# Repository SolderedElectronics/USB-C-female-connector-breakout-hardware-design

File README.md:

# USB-C female connector breakout Hardware Design

## About the Product

|  |
| :----------------------------------------------------------: |
| [Buy USB-C female connector breakout](https://www.solde.red/333011) |

The USB Type-C is ubiquitous. We always wanted to add it to our electronics projects, and we’re sure you did too. Adding a USB Type-C connector to your projects is easier than ever thanks to this USB Type-C breakout board. It will allow you to send data to your device, as well as add power to the circuit.

The USB Type-C connector’s GND, CC2, SBU2, D-, D+, SBU1, CC1, and VUSB pins are broken out to the plated through-holes.

---

## Repository Contents

This repository contains all design files for USB-C female connector breakout, organized as follows:

- **`CAD` folder**: Contains KiCAD design files, including:
  - Schematics
  - PCB layout
  - Panel PCB layout
  - Source 3D files in Fusion360, if any
  - All files are sorted by version with a detailed change log.
- **`OUTPUTS` folder**: Includes all production-ready files, such as:
  - Bill of Materials (BOM) and interactive BOM (iBOM)
  - PDF versions of schematics
  - 3D `.step` file of the board
  - 3D-printable models
  - Gerber files for PCB manufacturing
  - Image of the pinout of the board
  - Product image
  - Compliance, legal and generic sales documents

Refer to the `Change Log` in the CAD folder for details about updates between versions.

---

## Learn More About the Product

Beyond the repository, explore the following resources:

### Soldered Verify

The **Soldered Verify** system ensures every board you purchase from Soldered is fully functional. It also provides access to exclusive test data for your product. To get started, find the unique Soldered Verify ID on your product's packaging and enter the ID on the [Soldered Verify page](https://soldered.com/verify/) to access test results and additional product details.

### Soldered Community

Soldered Community is your go-to place for technical support. Our engineers track and answer all questions posted there, and it’s a great space for the maker community. Get answers to your questions and solutions for your challenges at [Soldered Community](https://soldered.com/community).

### solde.red

solde.red is an ultimate URL shortener and information hub. Access it by typing solde.red/ followed by your product SKU, e.g., [solde.red/333000](https://solde.red/333000), to find getting-started guides, datasheets, open-source hardware and software files, certifications, images, pinouts, and more. Read more about the shortener [here](https://solde.red/info/).

---

## Contributing

Contributions are welcome! Here’s how you can get involved:

- Submit pull requests to enhance the design or fix issues.
- Report bugs or problems by opening an issue.

We encourage community collaboration to make this product even better.

---

## About Soldered

[Soldered for Makers](https://soldered.com) specializes in designing and manufacturing electronic products tailored for enthusiasts, ranging from hobbyists to professionals. Our portfolio includes electronic boards, sensors, and actuators that are widely utilized in fields such as microelectronics, mechatronics, robotics, programming, and IoT. Every product we offer is designed in-house and built upon open-source hardware and software platforms. Proudly certified and manufactured within the European Union, our catalog likely includes the product you need for your project.

We complement these products with comprehensive tutorials and manuals, product descriptions, schematics, programming codes, and project examples. Our round-the-clock [customer and technical support](https://soldered.com/community) is available for all our products, irrespective of the sales channel. Soldered’s success and services reflect our maker community’s unwavering [trust](https://www.trustpilot.com/review/soldered.com), for which we are deeply grateful. Join our community and create using Soldered products.

---

## License

All Soldered open-source hardware (OSH) is under The TAPR Open Hardware License. Read more in the LICENSE file located in this repository.

**Disclaimer:**

No warranty - all designs in this repository are distributed in the hope that they will be useful, but without any warranty. They are provided "AS IS", therefore without warranty of any kind, either expressed or implied. The entire quality and performance of what you do with the contents of this repository are your responsibility. In no event Soldered Electronics will be liable for your damages, or losses, including any general, special, incidental, or consequential damage arising out of the use or inability to use the contents of this repository. 

---

## Have fun!

Thank you for your support from your fellow makers at Soldered Electronics.

Happy Making!

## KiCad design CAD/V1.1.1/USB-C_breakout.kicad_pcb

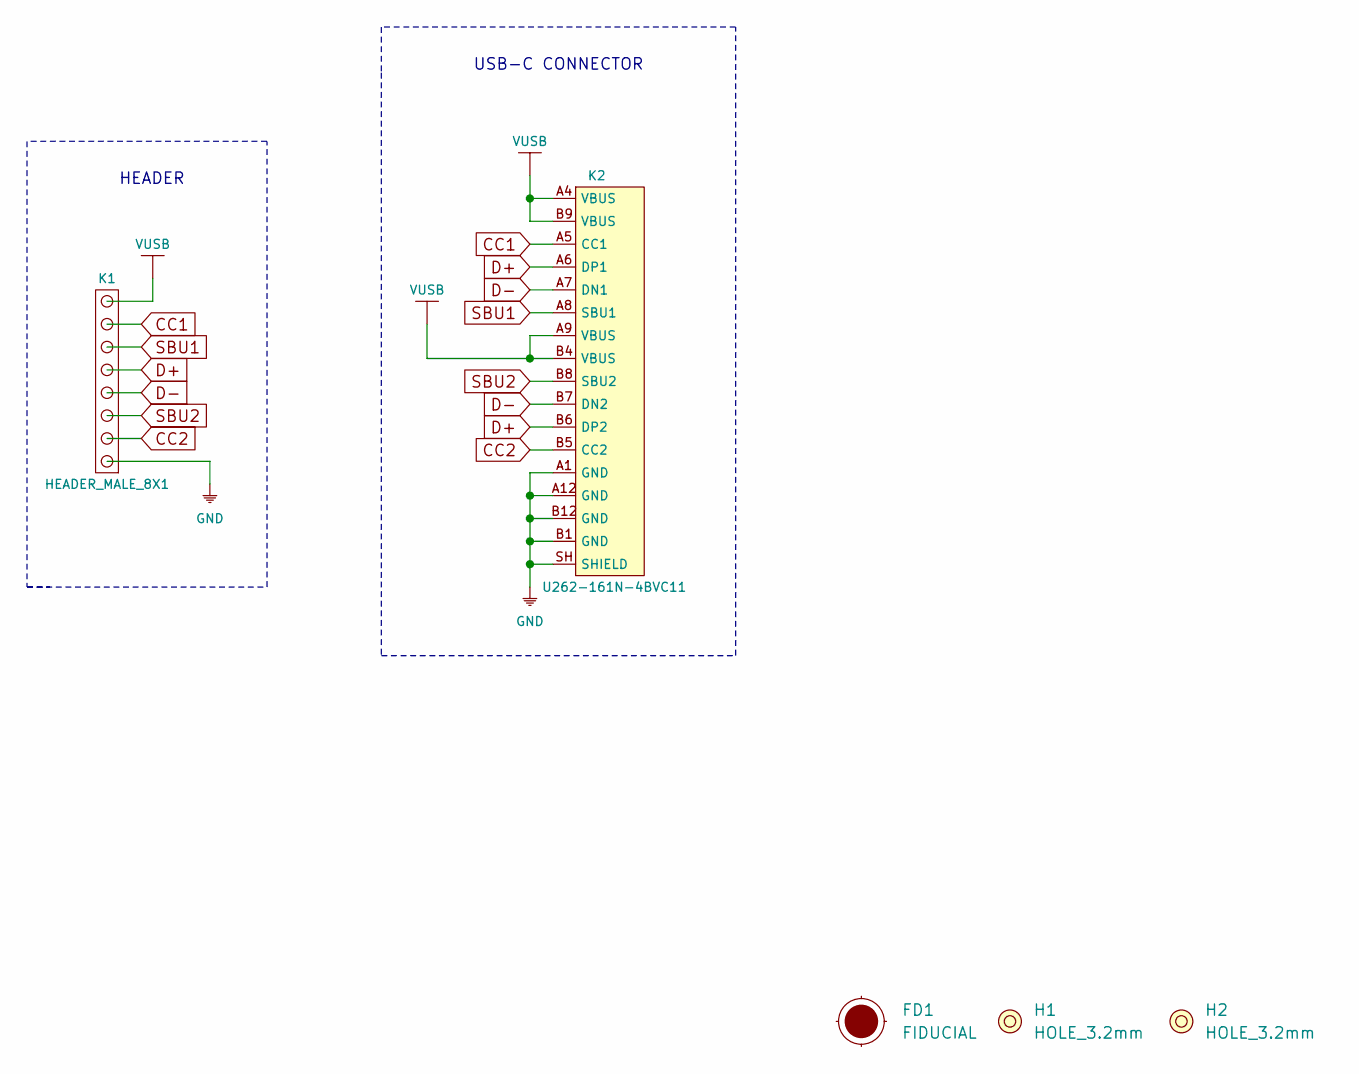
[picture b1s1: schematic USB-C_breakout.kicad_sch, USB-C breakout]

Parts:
FD1: FIDUCIAL; FIDUCIAL_23
H1, H2: HOLE_3.2mm
K1: HEADER_MALE_8X1
K2: U262-161N-4BVC11

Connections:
CC1: K1.7, K2.A5 (CC1)
CC2: K1.2, K2.B5 (CC2)
D+: K1.5, K2.A6 (DP1), K2.B6 (DP2)
D-: K1.4, K2.A7 (DN1), K2.B7 (DN2)
GND: K1.1, K2.A1 (GND), K2.A12 (GND), K2.B1 (GND), K2.B12 (GND), K2.SH (SHIELD)
SBU1: K1.6, K2.A8 (SBU1)
SBU2: K1.3, K2.B8 (SBU2)
VUSB: K1.8, K2.A4 (VBUS), K2.A9 (VBUS), K2.B4 (VBUS), K2.B9 (VBUS)

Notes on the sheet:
HEADER
USB-C CONNECTOR

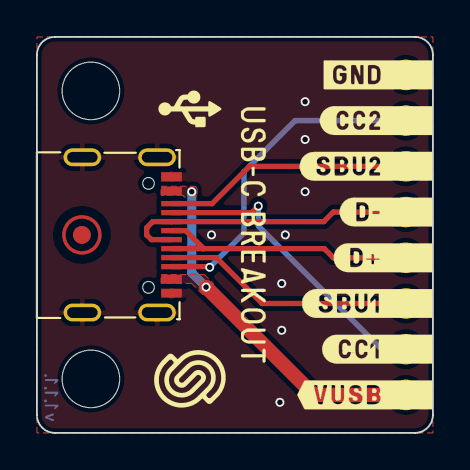
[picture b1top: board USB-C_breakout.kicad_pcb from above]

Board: 2 copper layers, 22.0 x 22.0 mm, 5 parts (1 on the bottom side), 8 nets.

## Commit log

2022-08-06 Updating open source files.
